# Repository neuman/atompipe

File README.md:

# nopekit

<p align="center">
<picture>
  <source media="(prefers-color-scheme: dark)" srcset="docs/img/nopey.png">
  
</picture>
</p>

## What Is Nopekit?

**Nopekit gives your AI agent engineering checks that can say “nope.”** It's a plugin for Claude Code, Codex and Cursor that helps you turn an idea into a physical design, test it against math, physics and engineering tools, and see what still needs work.

It's based on the [Grounding by Falsification](https://github.com/neuman/nopekit/blob/main/grounding_by_falsification.pdf) approach. AI has gotten very good at making believable proposals for all sorts of things both digital and physical but it is especially good at coding. The problem is that it's still not great at figuring out which proposals are actually good on its own. Grounding by falsification is the idea that we need to wrap AI with something outside itself that can check its work and say "nope" using trusted reasoning/math/physics/etc. Nopekit turns that approach into an extensible framework with room for plugins that can falsify proposals across any domain but especially physical design work.

**You describe what you want. The agent proposes a design. Independent checks try to break it.** Nopekit records the results and the reasons behind each design choice, then shows them on a project site. When the design changes, affected results become stale until checked again. Assumptions and tests that need a real prototype stay visible.

For example: “This shelf must carry 10 kg” becomes a load and a deflection limit. The agent designs a bracket; a beam check rejects it if it sags too far; a printability check rejects walls that are too thin. You can follow what failed, what changed, and why the next candidate is better.

[See It In Action](#see-it-in-action) · [Built In Packs](#built-in-packs) · [External Packs](#external-packs) · [Getting Started](#getting-started)

## See It In Action

**[PETGasus](https://neuman.github.io/PETGasusDrone/) is a quadcopter with a frame designed to print in one piece.** Its project site connects the design you can see with the requirements, decisions and evidence behind it.

[**Explore the live site →**](https://neuman.github.io/PETGasusDrone/) · [**Read the project repository →**](https://github.com/neuman/petgasusdrone)

The design history includes disconnected frames, thin walls and a frame that sagged far more than its optimizer predicted. Those rejected candidates are part of the record. The site shows what passed, what failed and what still waits on a physical build.

For smaller starting points, explore the [bracket example](examples/bracket/README.md), which runs without extra dependencies, or the [motorcycle airflow example](examples/motorbike/README.md), which uses OpenFOAM and ParaView.

## Built In Packs

Packs give the agent tools for a domain. A **proposer** makes a candidate; a **falsifier**, called a **gate**, checks it. One design can use several packs: a drone frame needs structural, printing, geometry and cost checks.

**Falsifiers**

These eleven packs ship with Nopekit. The images show designs, results or illustrations of what each pack can check; click a pack name for its gates, sources, setup and limits.

| Example | Pack and what it checks | Basis and sources |
|---|---|---|
| <br>Check the exported shape with a different solver | [**topology-simp**](packs/topology-simp/PACK.md) · 4 gates<br>Material volume, static displacement and stress in a stated region. CalculiX meshes the exported STL independently of the optimizer; checks include mesh refinement and load equilibrium. | **3 established · 1 model-only**<br>trimesh and CalculiX results, with model-input guards. Requires trimesh, NumPy, Gmsh and CalculiX 2.21. Linear isotropic static checks; printing and physical tests remain separate. |
| <br>Air around a motorcycle and rider | [**aero-openfoam**](packs/aero-openfoam/PACK.md) · 9 gates<br>Drag, mesh quality, convergence and wall treatment for turbulent external flow. The motorcycle example's drag claim is still unresolved. | **3 established · 4 sourced · 2 model-only**<br>OpenFOAM; published domain, convergence and grid-error methods. Needs ESI OpenFOAM v2606; ParaView 6.2 for pictures. |
| <br>Do all these parts fit together? | [**cad-solid**](packs/cad-solid/PACK.md) · 7 gates<br>Closed solids, collisions, wall thickness and whether every part is held in the assembly. | **1 established · 6 model-only**<br>trimesh's volume verdict; Nopekit's geometry checks. Needs trimesh and NumPy. |
| <br>A drone frame designed to print in one piece | [**fdm-print**](packs/fdm-print/PACK.md) · 7 gates<br>Thin walls, overhangs, bridges, bed fit, layer direction and estimated print time. | **7 model-only**<br>Printing heuristics with documented thresholds. Mesh checks need trimesh and NumPy. A pass still needs a real print. |
| <br>Check the board the router produced | [**pcb-kicad**](packs/pcb-kicad/PACK.md) · 10 gates<br>Design rules, open connections, schematic agreement, trace heating, circuit simulation and enclosure fit. | **6 established · 3 sourced · 1 model-only**<br>KiCad, ngspice and CadQuery; IPC-2221 and fabricator limits. A clean rule check does not establish a correct circuit. |
| <br>Beam-pack baseline, illustrated | [**beam-analytic**](packs/beam-analytic/PACK.md) · 8 gates<br>Bending, sag, buckling, shear and fastener bearing, with guards on where beam theory applies. | **7 sourced · 1 model-only**<br>Standard strength-of-materials formulae. No extra dependencies. Applies to beam-like members, not arbitrary meshes. |
| <br>Pressure loss through an oil channel | [**cfd-openfoam**](packs/cfd-openfoam/PACK.md) · 6 gates<br>Laminar pressure drop after checking flow regime, mesh quality, convergence and mesh independence. | **3 established · 2 sourced · 1 model-only**<br>OpenFOAM and published grid-convergence methods. Needs ESI OpenFOAM v2606; ParaView 6.2 for pictures. |
| <br>Solar charging over two weeks | [**thermal-analytic**](packs/thermal-analytic/PACK.md) · 10 gates<br>Heat loss, cooling, temperature, fins, solar collection and stagnation. | **9 sourced · 1 model-only**<br>Heat-transfer correlations; Duffie & Beckman and ASHRAE solar models. No extra dependencies. |
| <br>A solar Stirling system over a day | [**openmodelica**](packs/openmodelica/PACK.md) · 8 gates<br>Equation balance, compilation, simulation completion and simulated values against their limits. | **4 established · 4 model-only**<br>OpenModelica's own checks and results, plus source and consistency checks. Solver gates need `omc`. |
| <br>A hull that must float and stay upright | [**fluids-analytic**](packs/fluids-analytic/PACK.md) · 7 gates<br>Buoyancy, freeboard, stability, drag and pipe pressure loss. | **7 sourced**<br>Textbook hydrostatics and flow correlations, within their stated regimes. No extra dependencies. |
| <br>The whole build against its budget | [**sourcing**](packs/sourcing/PACK.md) · 7 gates<br>Missing prices, cost overruns, lead times, minimum orders and single-source parts. | **1 sourced · 6 model-only**<br>Vendor process rules and procurement checks on your recorded bill of materials. Offline; no live stock search. No extra dependencies. |

**How much should you trust a check?** Each gate declares where its logic comes from:

- **Established:** an existing tool's own verdict, such as KiCad's design-rule check. Trust extends as far as that tool and the problem you gave it.
- **Sourced:** a formula or rule from a cited textbook, standard or datasheet. Trust depends on the source and its range of applicability.
- **Model-only:** logic without an independent source. Its controls show it can fail; they do not establish that its reasoning is correct.

Before a gate's passes count, it must pass a known-good input and reject a known-bad one. That qualification is separate from its basis. **Skipped, crashed and stale checks never count as passes.** The report shows both the outcome and the basis so you can judge the evidence.

**Proposers**

The agent itself is the everyday proposer, writing and changing your design. Built-in packs also ship dedicated proposal tools:

| Example | Proposer | Tool and trust |
|---|---|---|
| <br>Find where the material earns its weight | [**topology-simp: 3D topology optimization**](packs/topology-simp/PACK.md)<br>Give it loads, supports, keep-outs and a material budget. SIMP proposes a 3D density field for your model to turn into a part. | **Sourced:** SIMP, density filtering and projection from published methods. Extracted from PETGasus. NumPy, SciPy and Numba; pyamg for larger solves. Its own score is a proposal, never structural proof. |
| <br>Routed keyboard board | [**pcb-kicad: autoroute**](packs/pcb-kicad/PACK.md)<br>Turn an unrouted KiCad board into a routed candidate. | **Freerouting**, an established autorouter. Its output is a proposal; KiCad gates check the adopted board. Requires pcbnew, Java and Freerouting. |

## External Packs

**A pack can live in its own Git repository.** You can share domain knowledge, wrap another engineering tool, or keep a project's custom checks alongside its design without changing Nopekit itself.

A standalone pack has a `pack.json` manifest, a `PACK.md` explaining its scope, and the gates, proposers, references and test fixtures it needs. Clone it into your project's `.nopekit/packs/<pack-name>/`, or into `~/.nopekit/packs/<pack-name>/` to make it discoverable across projects. `NOPEKIT_PACK_PATH` can point to other directories containing packs.

Then enable it by the name in its manifest:

```sh
nopekit packs list
nopekit packs validate <pack-name>
nopekit packs add <pack-name>
nopekit gate selftest --pack <pack-name>
```

`packs add` enables a discovered pack for the current project; cloning and updating its repository are separate steps. External gates also face mutation checks: Nopekit perturbs values from their known-good inputs to test whether the gates reject violations.

External packs can add specialized falsifiers, such as a product's crash or vibration tests, and proposal tools for domains the built-in packs do not yet cover.

To build your own, ask the agent to use Nopekit's **pack-authoring** skill. The [pack format](docs/PACK_FORMAT.md) defines the interface and the [extension protocol](docs/EXTENSION_PROTOCOL.md) explains how to develop and qualify a new capability.

## Getting Started

### 1. Install Nopekit

Nopekit is one plugin for three agents: the repository root holds a manifest for each
(`.claude-plugin/`, `.codex-plugin/`, `.cursor-plugin/`), and they share the same skills
and the same end-of-turn hook, which records each round.

**Claude Code.** Ask it:

> Install the Nopekit plugin from `https://github.com/neuman/nopekit` and help me get it ready to use.

Or install it directly with Claude Code's plugin commands:

```text
/plugin marketplace add neuman/nopekit
/plugin install nopekit
```

**Codex.** Codex reads the same marketplace:

```bash
codex plugin marketplace add neuman/nopekit
codex plugin add nopekit@nopekit
```

Codex runs a plugin's hook only after you review and trust it, and asks again after
every update of the plugin. Until you do, rounds are not recorded at the end of a turn;
`nopekit round --commit` records one by hand.

**Cursor.** Clone the plugin into Cursor's local plugins, then restart Cursor:

```bash
git clone --depth 1 https://github.com/neuman/nopekit ~/.cursor/plugins/local/nopekit
```

To update, `git -C ~/.cursor/plugins/local/nopekit pull` and restart. Cursor can also
import the Claude Code plugin; install it one way, not both, or each turn ends with two
rounds.

You'll need Python 3.10 or newer available as `python3`. Nopekit's core has no third-party Python dependencies. Some checks need optional tools or packages; the agent should tell you when one is needed. For mesh checks used in 3D printing and solid-part work, install:

```sh
pip install trimesh numpy
```

### 2. Bring an idea

Open your agent in a project directory and say:

> I want to use Nopekit to design something new. Interview me about the idea, one question at a time. Help me turn what I want into requirements, explore possible designs, set up the project and its checks, and launch the project site so I can understand the design and follow its progress.

You can start with an empty folder, a sketch, existing CAD files or a half-finished design. The agent helps choose the relevant packs and explains any tools they need.

## Using Nopekit Step By Step

You work through this in conversation. The agent operates the tools; the project site lets you follow the work and question its conclusions.

1. **Describe the thing you want.** Say what it does, where it goes and what matters: size, load, price, materials, power or feel. The agent helps make those requirements concrete.
2. **Decide what would count as success.** Turn requirements into testable claims: “sags no more than 0.5 mm,” “fits this printer,” “costs under $150.” Identify which need calculations, simulations, measurements or human judgment.
3. **Explore candidates.** The agent builds the model or runs a proposer. It records the choices, their reasons and the alternatives that lost, so the next iteration can build on what you learned.
4. **Run checks and inspect failures.** Gates compare the candidate with its limits. Follow the evidence on the site, challenge assumptions, change the design and run again. A missing solver stays visible as a skipped check.
5. **Review what is ready.** The report separates current checks from assumptions, unresolved claims and physical tests. Changing the design invalidates affected evidence. Each milestone names what must be established before you spend on a prototype or fabrication.
6. **Build, measure and feed the results back.** Export reruns the required checks before producing a package. Record what happened to the real article; a physical failure becomes evidence for the next design. A simulation pass alone never establishes how the built object behaves.

<details>
<summary>Useful commands when you want to inspect the project directly</summary>

| Command | What it tells you or does |
|---|---|
| `nopekit status` | Current claims and their statuses. |
| `nopekit check` | Run the project's gates. |
| `nopekit report` | Readiness and the evidence behind it. |
| `nopekit why <name>` | Why a parameter, claim, requirement or decision is there. |
| `nopekit gap --propose` | Missing evidence and packs that might help. |
| `nopekit doctor` | Diagnose the environment, model and records. |
| `nopekit site serve --watch --detach` | Open a local server that watches project changes. |
| `nopekit site serve --stop` | Stop the detached server. |
| `nopekit --help` | All commands and options. |

</details>

## More Detail

- [The method](METHOD.md) — the principles Nopekit makes mechanical.
- [Pack format](docs/PACK_FORMAT.md) — gates, proposers, controls and source declarations.
- [Extension protocol](docs/EXTENSION_PROTOCOL.md) — developing new capabilities.
- [Site contract](docs/SITE_CONTRACT.md) — how the site represents designs and evidence.
- [Spine contract](docs/SPINE_CONTRACT.md) — the engine, records and its limits.
- [Origins](docs/ORIGINS.md) — the experience behind the method.
- [Grounding by Falsification paper](grounding_by_falsification.pdf) — the underlying approach.
- [Contributing](CONTRIBUTING.md) — working on Nopekit itself.

## Status and License

Nopekit is an early project. The core engine and bundled packs work, but interfaces may change and the range of supported checks is still growing. Use it, inspect it, fork it, and tell us what breaks.

Licensed under the [Apache License 2.0](LICENSE).

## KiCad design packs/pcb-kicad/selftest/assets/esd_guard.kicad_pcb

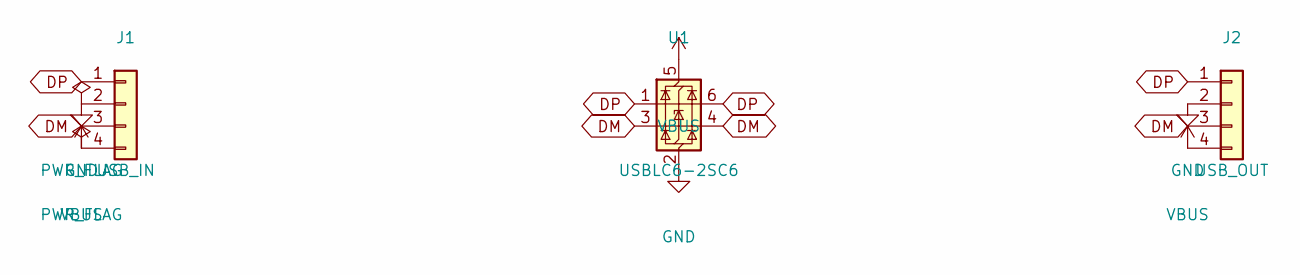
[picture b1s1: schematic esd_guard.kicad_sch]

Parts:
J1: USB_IN; PinHeader_1x04_P2.54mm_Vertical
J2: USB_OUT; PinHeader_1x04_P2.54mm_Vertical
U1: USBLC6-2SC6; SOT-23-6

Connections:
DM: J1.3, J2.3, U1.3 (I/O2), U1.4 (I/O2)
DP: J1.1, J2.1, U1.1 (I/O1), U1.6 (I/O1)
GND: J1.2, J2.2, U1.2 (GND)
VBUS: J1.4, J2.4, U1.5 (VBUS)

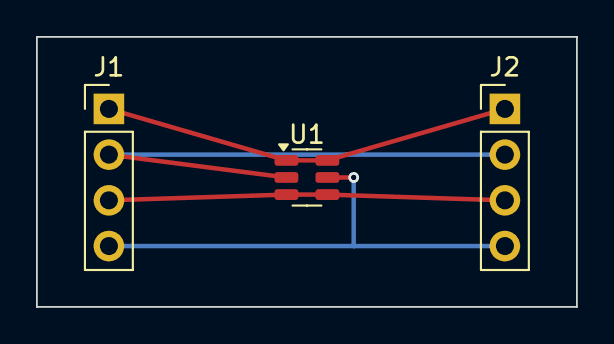
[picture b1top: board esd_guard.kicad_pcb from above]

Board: 2 copper layers, 30.0 x 15.0 mm, 3 parts (0 on the bottom side), 4 nets.
